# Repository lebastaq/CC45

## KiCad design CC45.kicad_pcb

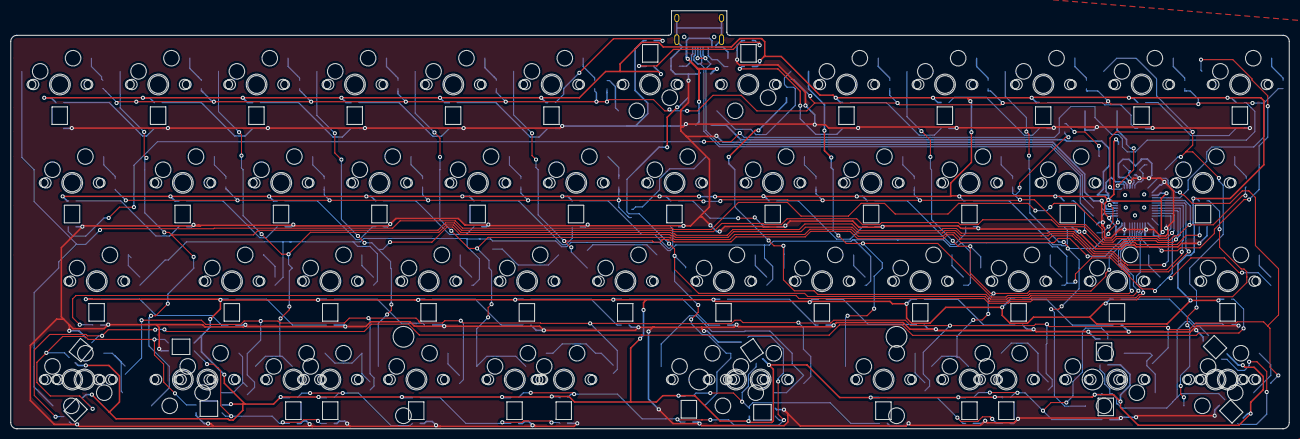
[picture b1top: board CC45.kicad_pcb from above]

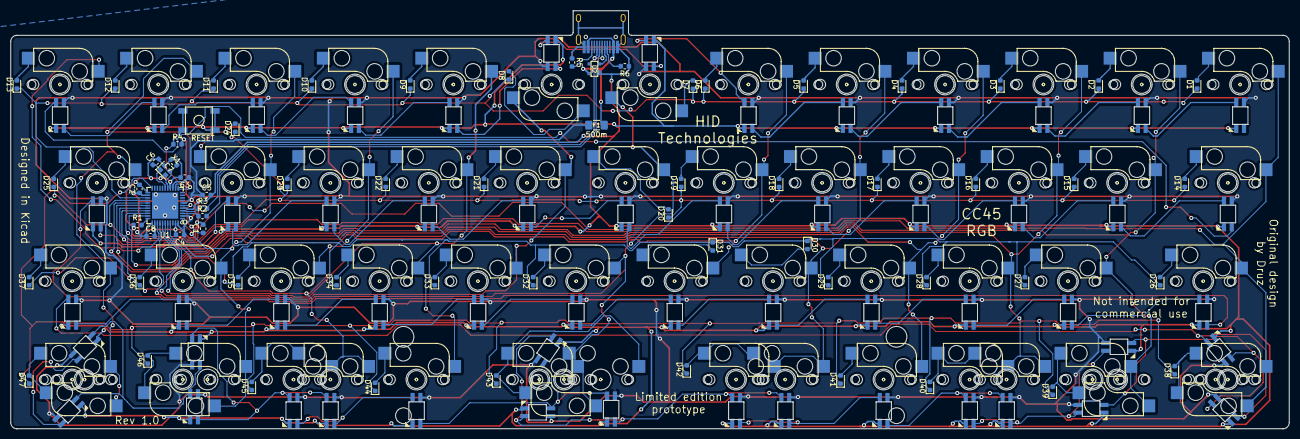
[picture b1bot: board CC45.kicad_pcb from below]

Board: 2 copper layers, 247.0 x 80.8 mm, 123 parts (67 on the bottom side), 125 nets.

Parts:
C1: 1u; C_0603_1608Metric
C2, C3, C4, C8: 0.1u; C_0603_1608Metric
C5: 10u; C_0603_1608Metric
C6, C7: 22p; C_0603_1608Metric
D1, D2, D3, D4, D5, D6, D7, D8, D9, D10, D11, D12, D13, D14, D15, D16, D17, D18, D19, D20, D21, D22, D23, D24, D25, D26, D27, D28, D29, D30, D31, D32, D33, D34, D35, D36, D37, D38, D39, D40, D41, D42, D43, D44, D45, D46, D47: D; D_0603_1608Metric
F1: 500m; Fuse_1206_3216Metric_Pad1.42x1.75mm_HandSolder
R1, R4: 10k; R_0603_1608Metric
R2, R3: 22; R_0603_1608Metric
R5, R6: 5.1k; R_0603_1608Metric
SW1: RESET; SKQG-1155865
SW2: K00; ChocMx_Socket
SW3: K01; ChocMx_Socket
SW4: K02; ChocMx_Socket
SW5: K03; ChocMx_Socket
SW6: K04; ChocMx_Socket
SW7: K05; ChocMx_Socket
SW8: K06; ChocMx_Socket
SW9: K07; ChocMx_Socket
SW10: K08; ChocMx_Socket
SW11: K09; ChocMx_Socket
SW12: K0A; ChocMx_Socket
SW13: K0B; ChocMx_Socket
SW14: K0C; ChocMx_Socket
SW15: K10; ChocMx_Socket
SW16: K11; ChocMx_Socket
SW17: K12; ChocMx_Socket
SW18: K13; ChocMx_Socket
SW19: K14; ChocMx_Socket
SW20: K15; ChocMx_Socket
SW21: K16; ChocMx_Socket
SW22: K17; ChocMx_Socket
SW23: K18; ChocMx_Socket
SW24: K19; ChocMx_Socket
SW25: K1A; ChocMx_Socket
SW26: K1B; ChocMx_Socket
SW27: K20; ChocMx_Socket
SW28: K21; ChocMx_Socket
SW29: K22; ChocMx_Socket
SW30: K23; ChocMx_Socket
SW31: K24; ChocMx_Socket
SW32: K25; ChocMx_Socket
SW33: K26; ChocMx_Socket
SW34: K27; ChocMx_Socket
SW35: K28; ChocMx_Socket
SW36: K29; ChocMx_Socket
SW37: K2A; ChocMx_Socket
SW38: K2B; ChocMx_Socket
SW39, SW39#2: K30; ChocMx_Socket
SW40, SW40#2: K31; ChocMx_Socket
SW41, SW41#2: K32; ChocMx_Socket
SW42: K33; ChocMx_Socket
SW43, SW43#2: K34; ChocMx_Socket
SW44, SW44#2: K36; ChocMx_Socket
SW44#3: K36; mx_with_stabilizer
SW45: K38; ChocMx_Socket
SW46, SW46#2: K39; ChocMx_Socket
SW47, SW47#2: K3A; ChocMx_Socket
SW48, SW48#2: K3B; ChocMx_Socket
U1: ATmega32U4-AU; QFN44G-0.5-7X7MM
U2: PRTR5V0U2X; SOT143B
USB1: HRO-TYPE-C-31-M-12; HRO-TYPE-C-31-M-12-HandSoldering
X1: XTAL; Crystal_SMD_2016-4Pin_2.0x1.6mm

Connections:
/USB_N: R2.2, U2.2 (IO1), USB1.5 (DN2), USB1.7 (DN1)
/USB_P: R3.2, U2.3 (IO2), USB1.6 (DP1), USB1.8 (DP2)
D+: R3.1, U1.4 (D+)
D-: R2.1, U1.3 (D-)
GND: C1.2, C2.2, C3.2, C4.2, C5.2, C6.2, C7.2, C8.2, R1.1, R5.1, R6.1, SW1.1, SW1.3, SW2.12 (VSS), SW3.12 (VSS), SW4.12 (VSS), SW5.12 (VSS), SW6.12 (VSS), SW7.12 (VSS), SW8.12 (VSS), SW9.12 (VSS), SW10.12 (VSS), SW11.12 (VSS), SW12.12 (VSS), SW13.12 (VSS), SW14.12 (VSS), SW15.12 (VSS), SW16.12 (VSS), SW17.12 (VSS), SW18.12 (VSS), SW19.12 (VSS), SW20.12 (VSS), SW21.12 (VSS), SW22.12 (VSS), SW23.12 (VSS), SW24.12 (VSS), SW25.12 (VSS), SW26.12 (VSS), SW27.12 (VSS), SW28.12 (VSS), SW29.12 (VSS), SW30.12 (VSS), SW31.12 (VSS), SW32.12 (VSS), SW33.12 (VSS), SW34.12 (VSS), SW35.12 (VSS), SW36.12 (VSS), SW37.12 (VSS), SW38.12 (VSS), SW39.12 (VSS), SW39#2.12 (VSS), SW40.12 (VSS), SW40#2.12 (VSS), SW41.12 (VSS), SW41#2.12 (VSS), SW42.12 (VSS), SW43.12 (VSS), SW43#2.12 (VSS), SW44.12 (VSS), SW44#2.12 (VSS), SW44#3.12 (VSS), SW45.12 (VSS), SW46.12 (VSS), SW46#2.12 (VSS), SW47.12 (VSS), SW47#2.12 (VSS), SW48.12 (VSS), SW48#2.12 (VSS), U1.5 (UGND), U1.15 (GND), U1.23 (GND), U1.35 (GND), U1.43 (GND), U2.1 (GND), USB1.1 (GND), USB1.12 (GND), USB1.13 (SHIELD), X1.2, X1.4
unnamed: C1.1, U1.6 (UCAP)
unnamed: D1.2 (A), SW2.2
unnamed: D2.2 (A), SW3.2
unnamed: D3.2 (A), SW4.2
unnamed: D4.2 (A), SW5.2
unnamed: D5.2 (A), SW6.2
unnamed: D6.2 (A), SW7.2
unnamed: D7.2 (A), SW8.2
unnamed: D8.2 (A), SW9.2
unnamed: D9.2 (A), SW10.2
unnamed: D10.2 (A), SW11.2
unnamed: D11.2 (A), SW12.2
unnamed: D12.2 (A), SW13.2
unnamed: D13.2 (A), SW14.2
unnamed: D14.2 (A), SW15.2
unnamed: D15.2 (A), SW16.2
unnamed: D16.2 (A), SW17.2
unnamed: D17.2 (A), SW18.2
unnamed: D18.2 (A), SW19.2
unnamed: D19.2 (A), SW20.2
unnamed: D20.2 (A), SW21.2
unnamed: D21.2 (A), SW22.2
unnamed: D22.2 (A), SW23.2
unnamed: D23.2 (A), SW24.2
unnamed: D24.2 (A), SW25.2
unnamed: D25.2 (A), SW26.2
unnamed: D26.2 (A), SW27.2
unnamed: D27.2 (A), SW28.2
unnamed: D28.2 (A), SW29.2
unnamed: D29.2 (A), SW30.2
unnamed: D30.2 (A), SW31.2
unnamed: D31.2 (A), SW32.2
unnamed: D32.2 (A), SW33.2
unnamed: D33.2 (A), SW34.2
unnamed: D34.2 (A), SW35.2
unnamed: D35.2 (A), SW36.2
unnamed: D36.2 (A), SW37.2
unnamed: D37.2 (A), SW38.2
unnamed: D38.2 (A), SW39.2, SW39#2.2
unnamed: D39.2 (A), SW40.2, SW40#2.2
unnamed: D40.2 (A), SW41.2, SW41#2.2
unnamed: D41.2 (A), SW42.2
unnamed: D42.2 (A), SW43.2, SW43#2.2
unnamed: D43.2 (A), SW44.2, SW44#2.2, SW44#3.2
unnamed: D44.2 (A), SW45.2
unnamed: D45.2 (A), SW46.2, SW46#2.2
unnamed: D46.2 (A), SW47.2, SW47#2.2
unnamed: D47.2 (A), SW48.2, SW48#2.2
unnamed: R1.2, U1.33 (~HWB~/PE2)
unnamed: R5.2, USB1.10 (CC2)
unnamed: R6.2, USB1.4 (CC1)
unnamed: SW2.9 (Dout), SW3.11 (Din)
unnamed: SW3.9 (Dout), SW4.11 (Din)
unnamed: SW4.9 (Dout), SW5.11 (Din)
unnamed: SW5.9 (Dout), SW6.11 (Din)
unnamed: SW6.9 (Dout), SW7.11 (Din)
unnamed: SW7.9 (Dout), SW8.11 (Din)
unnamed: SW8.9 (Dout), SW9.11 (Din)
unnamed: SW10.9 (Dout), SW11.11 (Din)
unnamed: SW9.9 (Dout), SW10.11 (Din)
unnamed: SW11.9 (Dout), SW12.11 (Din)
unnamed: SW12.9 (Dout), SW13.11 (Din)
unnamed: SW13.9 (Dout), SW14.11 (Din)
unnamed: SW14.9 (Dout), SW15.11 (Din)
unnamed: SW15.9 (Dout), SW16.11 (Din)
unnamed: SW16.9 (Dout), SW17.11 (Din)
unnamed: SW17.9 (Dout), SW18.11 (Din)
unnamed: SW18.9 (Dout), SW19.11 (Din)
unnamed: SW19.9 (Dout), SW20.11 (Din)
unnamed: SW20.9 (Dout), SW21.11 (Din)
unnamed: SW21.9 (Dout), SW22.11 (Din)
unnamed: SW22.9 (Dout), SW23.11 (Din)
unnamed: SW23.9 (Dout), SW24.11 (Din)
unnamed: SW24.9 (Dout), SW25.11 (Din)
unnamed: SW25.9 (Dout), SW26.11 (Din)
unnamed: SW26.9 (Dout), SW27.11 (Din)
unnamed: SW27.9 (Dout), SW28.11 (Din)
unnamed: SW28.9 (Dout), SW29.11 (Din)
unnamed: SW29.9 (Dout), SW30.11 (Din)
unnamed: SW30.9 (Dout), SW31.11 (Din)
unnamed: SW31.9 (Dout), SW32.11 (Din)
unnamed: SW32.9 (Dout), SW33.11 (Din)
unnamed: SW33.9 (Dout), SW34.11 (Din)
unnamed: SW34.9 (Dout), SW35.11 (Din)
unnamed: SW35.9 (Dout), SW36.11 (Din)
unnamed: SW36.9 (Dout), SW37.11 (Din)
unnamed: SW37.9 (Dout), SW38.11 (Din)
unnamed: SW38.9 (Dout), SW39.11 (Din), SW39#2.11 (Din)
unnamed: SW39.9 (Dout), SW39#2.9 (Dout), SW40.11 (Din), SW40#2.11 (Din)
unnamed: SW40.9 (Dout), SW40#2.9 (Dout), SW41.11 (Din), SW41#2.11 (Din)
unnamed: SW41.9 (Dout), SW41#2.9 (Dout), SW42.11 (Din)
unnamed: SW42.9 (Dout), SW43.11 (Din), SW43#2.11 (Din)
unnamed: SW43.9 (Dout), SW43#2.9 (Dout), SW44.11 (Din), SW44#2.11 (Din), SW44#3.11 (Din)
unnamed: SW44.9 (Dout), SW44#2.9 (Dout), SW44#3.9 (Dout), SW45.11 (Din)
unnamed: SW45.9 (Dout), SW46.11 (Din), SW46#2.11 (Din)
unnamed: SW46.9 (Dout), SW46#2.9 (Dout), SW47.11 (Din), SW47#2.11 (Din)
unnamed: SW47.9 (Dout), SW47#2.9 (Dout), SW48.11 (Din), SW48#2.11 (Din)
unnamed: SW48.9 (Dout), SW48#2.9 (Dout)
RESET: R4.1, SW1.2, SW1.4, U1.13 (~RESET)
VCC: F1.2, U2.4 (VCC), USB1.2 (VBUS), USB1.11 (VBUS)
Vcc: C2.1, C3.1, C4.1, C5.1, C8.1, F1.1, R4.2, SW2.10 (Vdd), SW3.10 (Vdd), SW4.10 (Vdd), SW5.10 (Vdd), SW6.10 (Vdd), SW7.10 (Vdd), SW8.10 (Vdd), SW9.10 (Vdd), SW10.10 (Vdd), SW11.10 (Vdd), SW12.10 (Vdd), SW13.10 (Vdd), SW14.10 (Vdd), SW15.10 (Vdd), SW16.10 (Vdd), SW17.10 (Vdd), SW18.10 (Vdd), SW19.10 (Vdd), SW20.10 (Vdd), SW21.10 (Vdd), SW22.10 (Vdd), SW23.10 (Vdd), SW24.10 (Vdd), SW25.10 (Vdd), SW26.10 (Vdd), SW27.10 (Vdd), SW28.10 (Vdd), SW29.10 (Vdd), SW30.10 (Vdd), SW31.10 (Vdd), SW32.10 (Vdd), SW33.10 (Vdd), SW34.10 (Vdd), SW35.10 (Vdd), SW36.10 (Vdd), SW37.10 (Vdd), SW38.10 (Vdd), SW39.10 (Vdd), SW39#2.10 (Vdd), SW40.10 (Vdd), SW40#2.10 (Vdd), SW41.10 (Vdd), SW41#2.10 (Vdd), SW42.10 (Vdd), SW43.10 (Vdd), SW43#2.10 (Vdd), SW44.10 (Vdd), SW44#2.10 (Vdd), SW44#3.10 (Vdd), SW45.10 (Vdd), SW46.10 (Vdd), SW46#2.10 (Vdd), SW47.10 (Vdd), SW47#2.10 (Vdd), SW48.10 (Vdd), SW48#2.10 (Vdd), U1.2 (UVCC), U1.7 (VBUS), U1.14 (VCC), U1.24 (AVCC), U1.34 (VCC), U1.44 (AVCC)
XTAL1: C6.1, U1.17 (XTAL1), X1.1
XTAL2: C7.1, U1.16 (XTAL2), X1.3
col0: SW2.1, SW15.1, SW27.1, SW39.1, SW39#2.1, U1.31 (PC6)
col1: SW3.1, SW16.1, SW28.1, SW40.1, SW40#2.1, U1.29 (PB5)
col2: SW4.1, SW17.1, SW29.1, SW41.1, SW41#2.1, U1.32 (PC7)
col3: SW5.1, SW18.1, SW30.1, SW42.1, U1.28 (PB4)
col4: SW6.1, SW19.1, SW31.1, SW43.1, SW43#2.1, U1.27 (PD7)
col5: SW7.1, SW20.1, SW32.1, U1.41 (PF0)
col6: SW8.1, SW21.1, SW33.1, SW44.1, SW44#2.1, SW44#3.1, U1.37 (PF6)
col7: SW9.1, SW22.1, SW34.1, U1.38 (PF5)
col8: SW10.1, SW23.1, SW35.1, SW45.1, U1.39 (PF4)
col9: SW11.1, SW24.1, SW36.1, SW46.1, SW46#2.1, U1.40 (PF1)
col10: SW12.1, SW25.1, SW37.1, SW47.1, SW47#2.1, U1.1 (PE6)
col11: SW13.1, SW26.1, SW38.1, SW48.1, SW48#2.1, U1.12 (PB7)
col12: SW14.1, U1.36 (PF7)
row0: D1.1 (K), D2.1 (K), D3.1 (K), D4.1 (K), D5.1 (K), D6.1 (K), D7.1 (K), D8.1 (K), D9.1 (K), D10.1 (K), D11.1 (K), D12.1 (K), D13.1 (K), U1.25 (PD4)
row1: D14.1 (K), D15.1 (K), D16.1 (K), D17.1 (K), D18.1 (K), D19.1 (K), D20.1 (K), D21.1 (K), D22.1 (K), D23.1 (K), D24.1 (K), D25.1 (K), U1.26 (PD6)
row2: D26.1 (K), D27.1 (K), D28.1 (K), D29.1 (K), D30.1 (K), D31.1 (K), D32.1 (K), D33.1 (K), D34.1 (K), D35.1 (K), D36.1 (K), D37.1 (K), U1.30 (PB6)
row3: D38.1 (K), D39.1 (K), D40.1 (K), D41.1 (K), D42.1 (K), D43.1 (K), D44.1 (K), D45.1 (K), D46.1 (K), D47.1 (K), U1.22 (PD5)

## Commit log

2020-07-04 start adding rgb
2020-07-04 routing
2020-07-04 2d line on schem
2020-07-04 moar routing
2020-07-04 who needs MCUs anyway
2020-07-05 add socket keep out zones
2020-07-05 switch to 0805
2020-07-05 switch to 0603
2020-07-05 fix drc
2020-07-05 routing lol
2020-07-05 routing lmao
2020-07-05 finish routing + zoning
2020-07-05 moar zoning
2020-07-05 finishing touches
2020-07-05 doot
2020-07-05 add text
2020-07-05 add vias in MCU
